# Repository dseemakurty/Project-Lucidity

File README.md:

Welcome to Project Lucidity

At its core, Project Lucidity is a sleep mask that helps you attain the elusive lucid dream. But this project is more than that. Its about taking the art of controlling your dreams and bringing it from a shaky phenomenon to a more understood science. To do so, Project Lucidity was designed as a fully featured, hobbyist and developer friendly, lucid dreaming mask that goes above and beyond. 

For more information about the project, check out the main website at: http://dseemakurty.wix.com/project-lucidity

All the code, schematics, and eagle files have been uploaded into this github. Feel free to utilize this information for your personal designs but please check the license file for any concerns about the contents use.

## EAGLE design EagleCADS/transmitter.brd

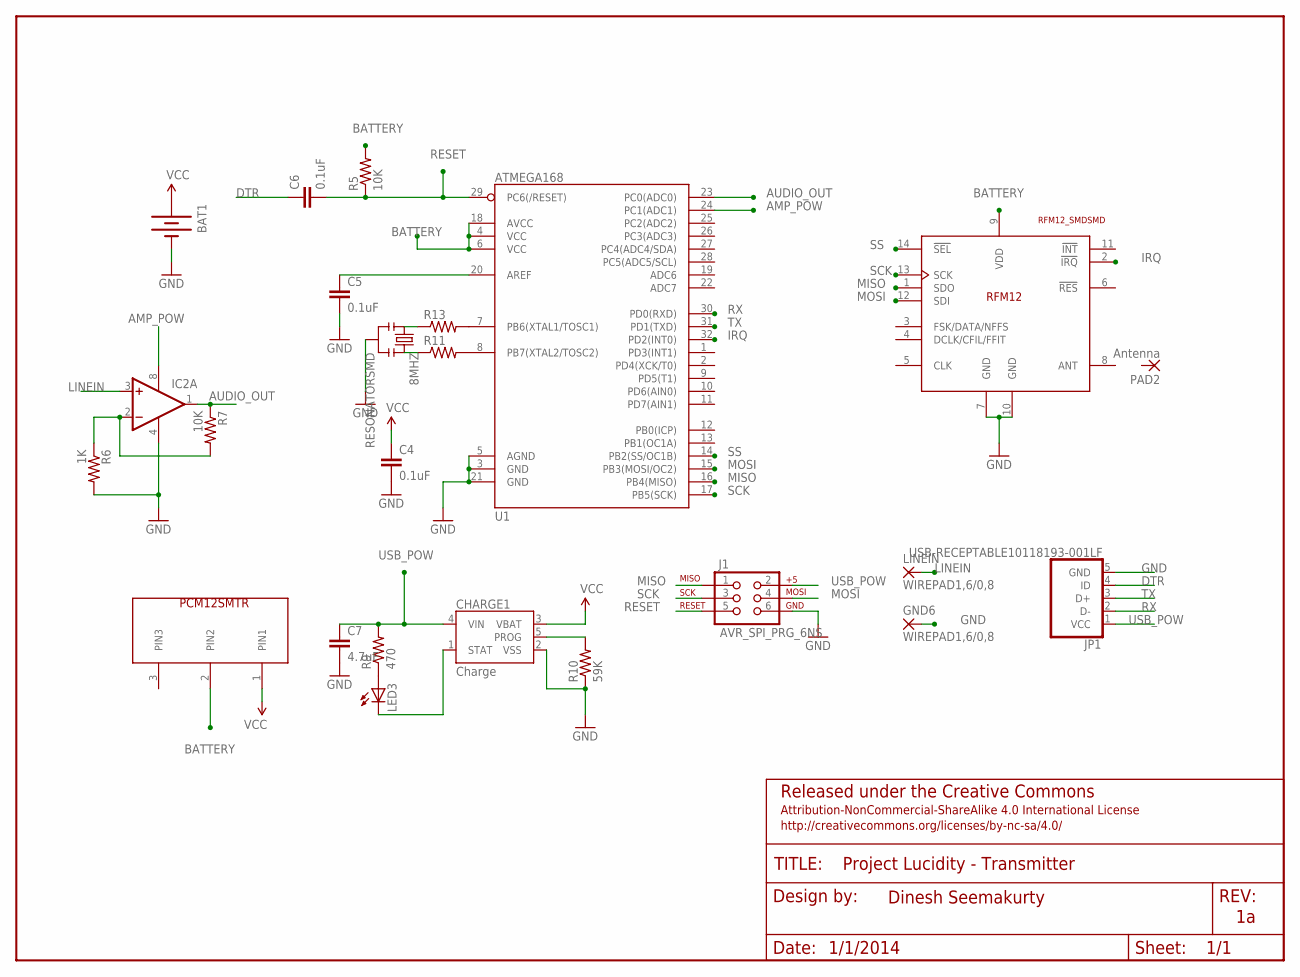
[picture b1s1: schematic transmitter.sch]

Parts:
8MHZ: RESONATORSMD; RESONATOR-SMD
BAT1: BATTERY20MM_4LEGS; BATTCON_20MM_4LEGS
C4, C5, C6: 0.1uF; 0805
C7: 4.7uF; 0805
CHARGE1: Charge; SOT23-5
FRAME1: FRAME-LETTER; CREATIVE_COMMONS
GND6: WIREPAD1,6/0,8; 1,6/0,8
IC2: LM358D; SO08
J1: AVR_SPI_PRG_6NS; 2X3-NS
JP1: USB-RECEPTABLE10118193-001LF; FCI-10118193-0001LF
LED3: LED0603; LED-0603
LINEIN: WIREPAD1,6/0,8; 1,6/0,8
PAD2: Antenna; SMD1,27-2,54
R5, R7: 10K; 0805
R6: 1K; 0805
R9: 470; 0805
R10: 59K; 0805
R11, R13: RESISTOR0402-RES; 0402-RES
U1: ATMEGA168; TQFP32-08
U$2: PCM12SMTR
U$3: RFM12_SMDSMD; RFM12

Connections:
AMP_POW: IC2.8 (V+), U1.24 (PC1(ADC1))
AUDIO_OUT: IC2.1 (OUT), R7.1, U1.23 (PC0(ADC0))
BATTERY: R5.2, U1.4 (VCC), U1.6 (VCC), U1.18 (AVCC), U$2.2 (PIN2), U$3.9 (VDD)
DTR: C6.1, JP1.4 (ID)
GND: 8MHZ.2, BAT1.GND (-), C4.2, C5.2, C7.2, CHARGE1.2 (VSS), GND6.1, IC2.4 (V-), J1.6, JP1.5 (GND), R6.2, R10.1, U1.3 (GND), U1.5 (AGND), U1.21 (GND), U$3.7 (GND), U$3.10 (GND)
IRQ: U1.32 (PD2(INT0)), U$3.2 (!IRQ)
LINEIN: IC2.3 (+IN), LINEIN.1
MISO: J1.1, U1.16 (PB4(MISO)), U$3.1 (SDO)
MOSI: J1.4, U1.15 (PB3(MOSI/OC2)), U$3.12 (SDI)
unnamed: R13.2, U1.7 (PB6(XTAL1/TOSC1))
unnamed: C5.1, U1.20 (AREF)
unnamed: R11.2, U1.8 (PB7(XTAL2/TOSC2))
unnamed: LED3.A, R9.1
unnamed: IC2.2 (-IN), R6.1, R7.2
unnamed: CHARGE1.1 (STAT), LED3.C
unnamed: CHARGE1.5 (PROG), R10.2
unnamed: 8MHZ.1, R13.1
unnamed: 8MHZ.3, R11.1
RESET: C6.2, J1.5, R5.1, U1.29 (PC6(/RESET))
RX: JP1.2 (D-), U1.30 (PD0(RXD))
SCK: J1.3, U1.17 (PB5(SCK)), U$3.13 (SCK)
SS: U1.14 (PB2(SS/OC1B)), U$3.14 (!SEL)
TX: JP1.3 (D+), U1.31 (PD1(TXD))
USB_POW: C7.1, CHARGE1.4 (VIN), J1.2, JP1.1 (VCC), R9.2
VCC: BAT1.POW1 (+), BAT1.POW2 (+), BAT1.POW3 (+), BAT1.POW4 (+), C4.1, CHARGE1.3 (VBAT), U$2.1 (PIN1)

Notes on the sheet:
Released under the Creative Commons
Attribution-NonCommercial-ShareAlike 4.0 International License
http://creativecommons.org/licenses/by-nc-sa/4.0/
Project Lucidity - Transmitter
Dinesh Seemakurty
1/1/2014

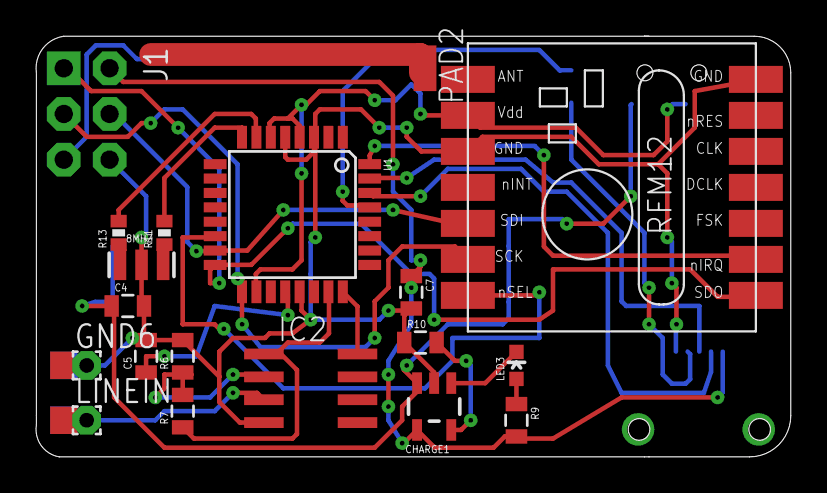
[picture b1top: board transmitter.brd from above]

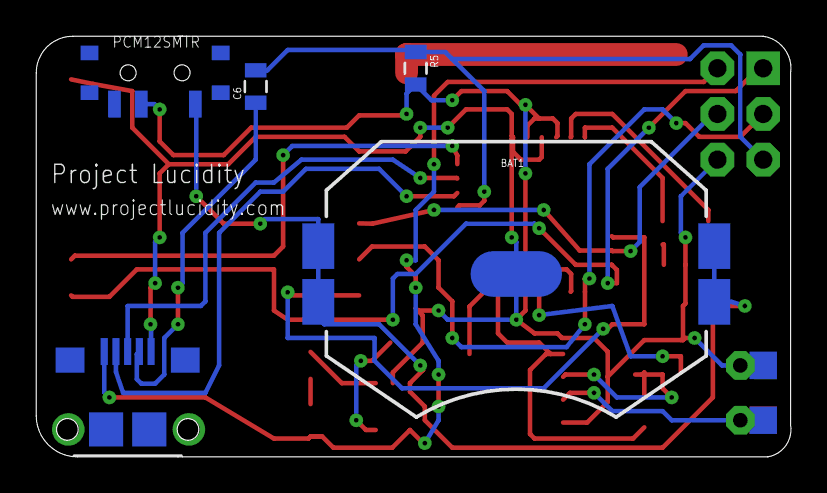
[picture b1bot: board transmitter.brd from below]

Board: 2 copper layers, 41.9 x 23.4 mm, 25 parts (5 on the bottom side), 25 nets.

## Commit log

2014-01-31 Adding Project Files
2014-01-31 Cleaning Up
2014-01-31 Adding README
2014-01-31 Correction

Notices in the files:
parts and their libraries:
SparkFun-DigitalIC: Licensing: CC v3.0 Share-Alike You are welcome to use this library for commercial purposes.
test: Released under the Creative Commons Attribution Non-Commercial Share-Alike 3.0 License
test: http://http://creativecommons.org/licenses/by-nc-sa/4.0
